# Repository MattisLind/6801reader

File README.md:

# 6801reader
This project aims at reading the ROM content out of a mask programmed MC6801 uP used in the Ericsson PC keyboard.

To help the MAME project to create a faithful emulation of the Ericsson PC I was asked to dump the ROM contents of a mask programmed 
6801 uProcessor which is the brain inside the keyboard. Compared to standard IBM PC the Ericsson PC make use of a completely different keyboard protocol
The protocol has standard serial communication rather than the clocked shiftregister approach in the IBM PC. In the receiving end on the mainboard there is a 8251 
serial communication IC. Dumping the keyboard and then emulating the MC6801 uProcessor inside MAME would then give a complete and faithful emulation of 
thenentire Ericsson PC.

## Dumping the 6801
Masked ROM can be a bit tricky to read out. On some uProcessor it isn't possible at all. On the 6801 there is a test mode 0 which 
makes the processor to behave a bit odd. It sets  the processor in non multiplexed mode which means that the 8 IO ports are the upper 8 bits of the address.
Then another IO port is the multiplexed Data and Adress bus for the lower 8 bits of the address. This is quite standard, but there
is another tweak that makes it possible to do the reading. In mode 0 it will also read the RESET vector from the external bus. It will disable reading
of the internal ROM for the two first cycles, thereby allowing external logic to map in external ROM for these two cycles and have the 
processor start the external program.

The external program can then be used to read all of the internal memory. Including the RESET vectors since after the two first access the internal address decoding goes back to
normal and the internal ROM RESET vectors can be read.

## Design

Adress decoding need special treatment during the first two cycles. This is achieved by a shiftregister that is shifting the RESET
signal when it transits from active to inactive. The three stage shiftregister is clocked by the negative edge of the E signal.
The result will be a delayed RESET signal. As long as the delayed RESET signal is low the deccoding will map addresses in the F800-FFFF range to
the external EPROM. After this period this decoding will be disabled and only accesses to F000-F7FF will be decoded as external.

The logic to handle the decoding and the shiftregister is implemented in a GAL16V8 PLD. The PLD also is used to debounce the RESET 
signal from the toggle switch.

## Firmware

The firmware used is a small debug monitor developed by Daniel Tufvesson [called MC3 monitor](http://www.waveguide.se/?article=mc3-monitor-13) which is modified 
to handle different memory locations for ROM and RAM. The 2.4576 MHz crystal result in a 4800 bps rate of the serial port.

The monitor can then be used to dump the ROM contents and transfer it to the host PC over the serial port.

The 2764 is a 8k EPROM with total address range 0000-1FFF.
This means that the 2k monitor code need to be in BOTH the 1000-17FF range and the 1800-1FFF range for the design to work. I.e. during the first two cycles it will access the 1800-1FFF range and after that the 1000-17FF range will be accessed. Actually repeating the monitor on all four 2k banks of the EPROM wouldn't harm at all. The PLD will select the proper range.

## Schemtic and layout.

A schematic has been created in KiCAD and a breadboard circuit. Possibly a layout is created as well.

## Mockup 

A mockup was created on a breadboard and a small problem was detected in the PLD. New PLD code fixed that problem. It was also detected that 68701 is sufficently different from the 6801 to not work with this circuit. The reason is that the 68701 has the interrupt vectors in a different place when running in mode 0. The 6803, which is the romless variant of the 6801, does work identical to the 6801. As it turns out it works perfectly with the circuit above. One interesting thing is that there actually are ROM content in the ROM which seems to be at least potentially correct. At least the RESET vector is in the correct spot! So it seems the 6803 is just 6801 chips which has been discarded due to bad firmware!? 

With the baudrate set to 4800 bps a 6803 or a 6801 processor gave us a ">" prompt in response to pressing the reset button. It was working! 

The resulting dump of the Ericsson keyboard 6801 firmware contained some interesting strings!

## PCB layout

A modified design and PCB layout were created with KiCad 9.0. The main change was to add a FT232 USB to serial IC. Additionally, A11 was reconnected to the EPROM, requiring the ROM to be put in all four banks as suggested above.

(modified design and layout by Tom Virostek (xuulan))

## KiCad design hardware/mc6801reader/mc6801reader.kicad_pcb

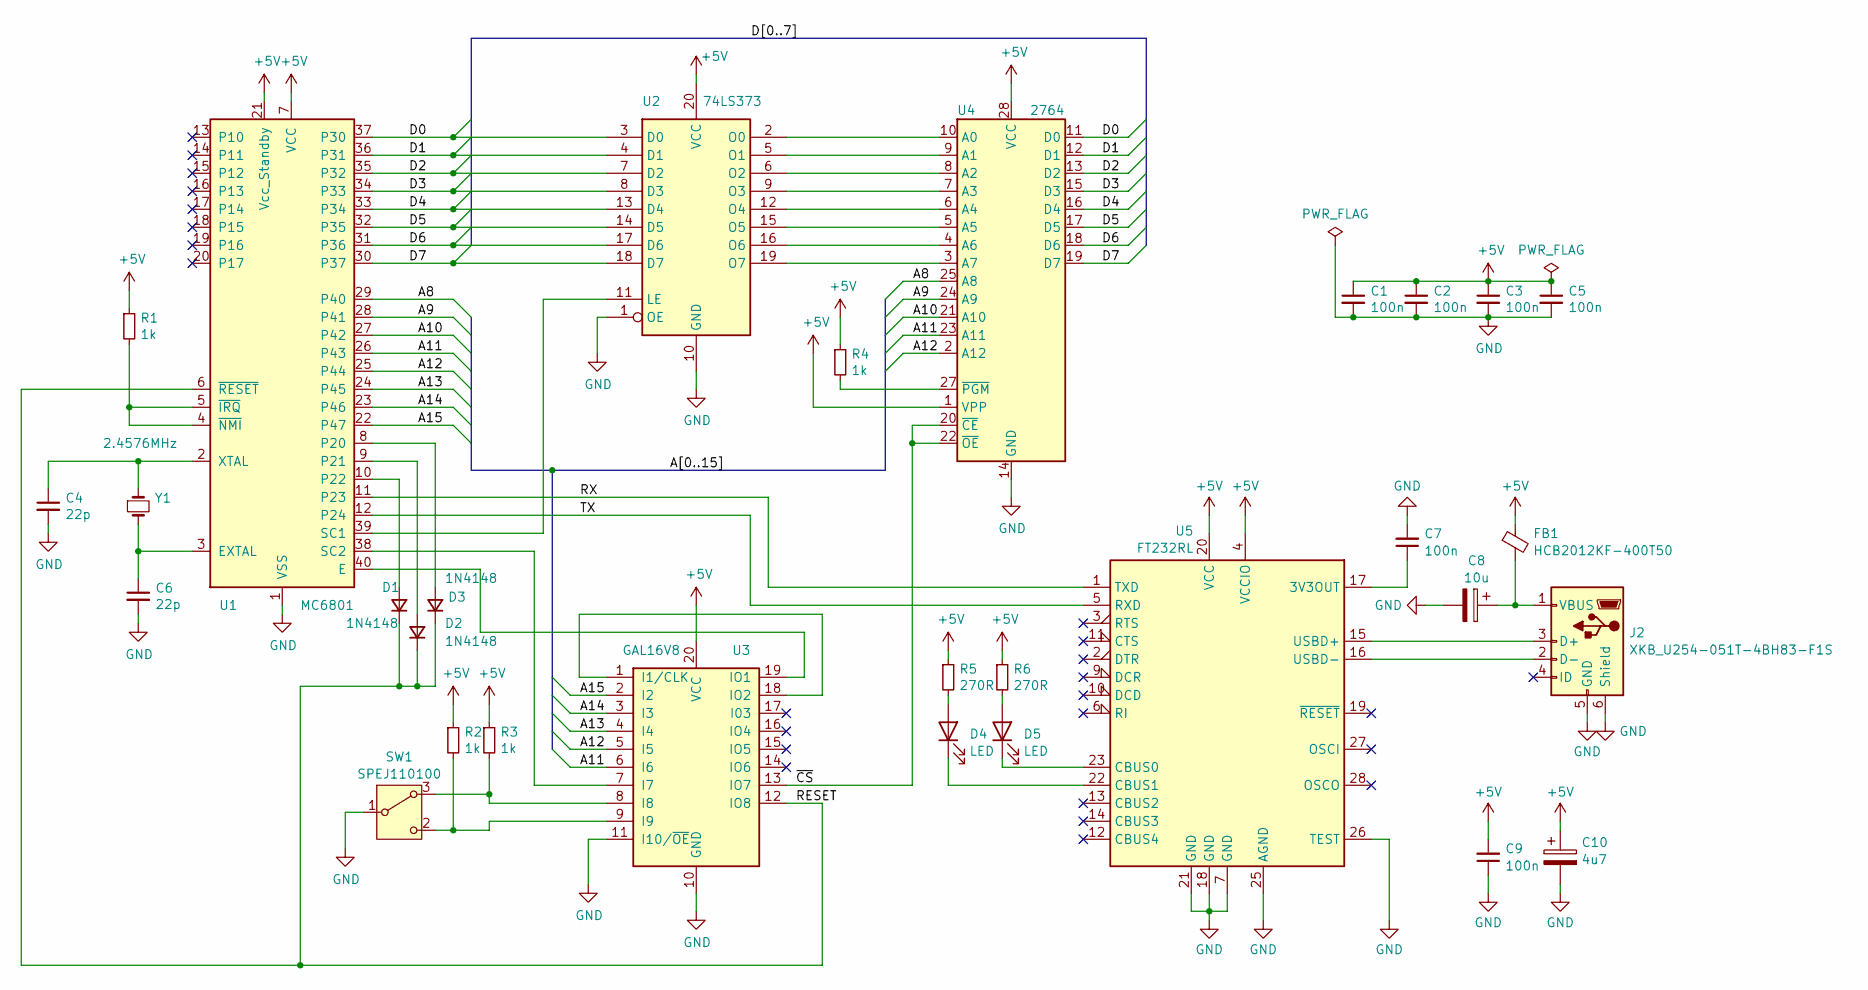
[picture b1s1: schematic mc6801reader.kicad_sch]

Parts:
C1, C2, C3, C5, C7, C9: 100n; C_0805_2012Metric
C4, C6: 22p; C_0805_2012Metric
C8: 10u; CP_EIA-3216-18_Kemet-A
C10: 4u7; CP_EIA-3216-18_Kemet-A
D1, D2, D3: 1N4148; D_SOD-323
D4, D5: LED; LED_0805_2012Metric
FB1: HCB2012KF-400T50; L_0805_2012Metric
J2: XKB_U254-051T-4BH83-F1S; USB_Micro-B_XKB_U254-051T-4BH83-F1S
R1, R2, R3, R4: 1k; R_0805_2012Metric
R5, R6: 270R; R_0805_2012Metric
SW1: SPEJ110100
U1: MC6801; DIP-40_W15.24mm
U2: 74LS373; SOIC-20W_7.5x12.8mm_P1.27mm
U3: GAL16V8; DIP-20_W7.62mm_Socket
U4: 2764; DIP-28_W15.24mm
U5: FT232RL; SSOP-28_5.3x10.2mm_P0.65mm
Y1: 2.4576MHz; Crystal_HC49-U_Vertical

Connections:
+5V: C1.1, C2.1, C3.1, C5.1, C9.2, C10.1, FB1.1, R1.1, R2.1, R3.1, R4.1, R5.1, R6.1, U1.7 (VCC), U1.21 (Vcc_Standby), U2.20 (VCC), U3.20 (VCC), U4.1 (VPP), U4.28 (VCC), U5.4 (VCCIO), U5.20 (VCC)
/A8: U1.29 (P40), U4.25 (A8)
/A9: U1.28 (P41), U4.24 (A9)
/A10: U1.27 (P42), U4.21 (A10)
/A11: U1.26 (P43), U3.6 (I6), U4.23 (A11)
/A12: U1.25 (P44), U3.5 (I5), U4.2 (A12)
/A13: U1.24 (P45), U3.4 (I4)
/A14: U1.23 (P46), U3.3 (I3)
/A15: U1.22 (P47), U3.2 (I2)
/D0: U1.37 (P30), U2.3 (D0), U4.11 (D0)
/D1: U1.36 (P31), U2.4 (D1), U4.12 (D1)
/D2: U1.35 (P32), U2.7 (D2), U4.13 (D2)
/D3: U1.34 (P33), U2.8 (D3), U4.15 (D3)
/D4: U1.33 (P34), U2.13 (D4), U4.16 (D4)
/D5: U1.32 (P35), U2.14 (D5), U4.17 (D5)
/D6: U1.31 (P36), U2.17 (D6), U4.18 (D6)
/D7: U1.30 (P37), U2.18 (D7), U4.19 (D7)
/RESET: D1.1 (K), D2.1 (K), D3.1 (K), U1.6 (~RESET), U3.12 (IO8)
/RX: U1.11 (P23), U5.1 (TXD)
/TX: U1.12 (P24), U5.5 (RXD)
/~CS: U3.13 (IO7), U4.20 (~CE), U4.22 (~OE)
GND: C1.2, C2.2, C3.2, C4.2, C5.2, C6.2, C7.2, C8.2, C9.1, C10.2, J2.5 (GND), J2.6 (Shield), SW1.1 (B), U1.1 (VSS), U2.1 (OE), U2.10 (GND), U3.10 (GND), U3.11 (I10/~OE), U4.14 (GND), U5.7 (GND), U5.18 (GND), U5.21 (GND), U5.25 (AGND), U5.26 (TEST)
unnamed: D1.2 (A), U1.10 (P22)
unnamed: D2.2 (A), U1.9 (P21)
unnamed: D3.2 (A), U1.8 (P20)
unnamed: D4.2 (A), R5.2
unnamed: D4.1 (K), U5.22 (CBUS1)
unnamed: D5.2 (A), R6.2
unnamed: D5.1 (K), U5.23 (CBUS0)
unnamed: J2.3 (D+), U5.15 (USBD+)
unnamed: J2.2 (D-), U5.16 (USBD-)
unnamed: C8.1, FB1.2, J2.1 (VBUS)
unnamed: R3.2, SW1.3 (A), U3.8 (I8)
unnamed: R2.2, SW1.2 (C), U3.9 (I9)
unnamed: U1.40 (E), U3.19 (IO1)
unnamed: C6.1, U1.3 (EXTAL), Y1.2
unnamed: U1.39 (SC1), U2.11 (LE)
unnamed: U1.38 (SC2), U3.7 (I7)
unnamed: C4.1, U1.2 (XTAL), Y1.1
unnamed: R1.2, U1.4 (~NMI), U1.5 (~IRQ)
unnamed: U2.2 (O0), U4.10 (A0)
unnamed: U2.5 (O1), U4.9 (A1)
unnamed: U2.6 (O2), U4.8 (A2)
unnamed: U2.9 (O3), U4.7 (A3)
unnamed: U2.12 (O4), U4.6 (A4)
unnamed: U2.15 (O5), U4.5 (A5)
unnamed: U2.16 (O6), U4.4 (A6)
unnamed: U2.19 (O7), U4.3 (A7)
unnamed: U3.1 (I1/CLK), U3.18 (IO2)
unnamed: R4.2, U4.27 (~PGM)
unnamed: C7.1, U5.17 (3V3OUT)

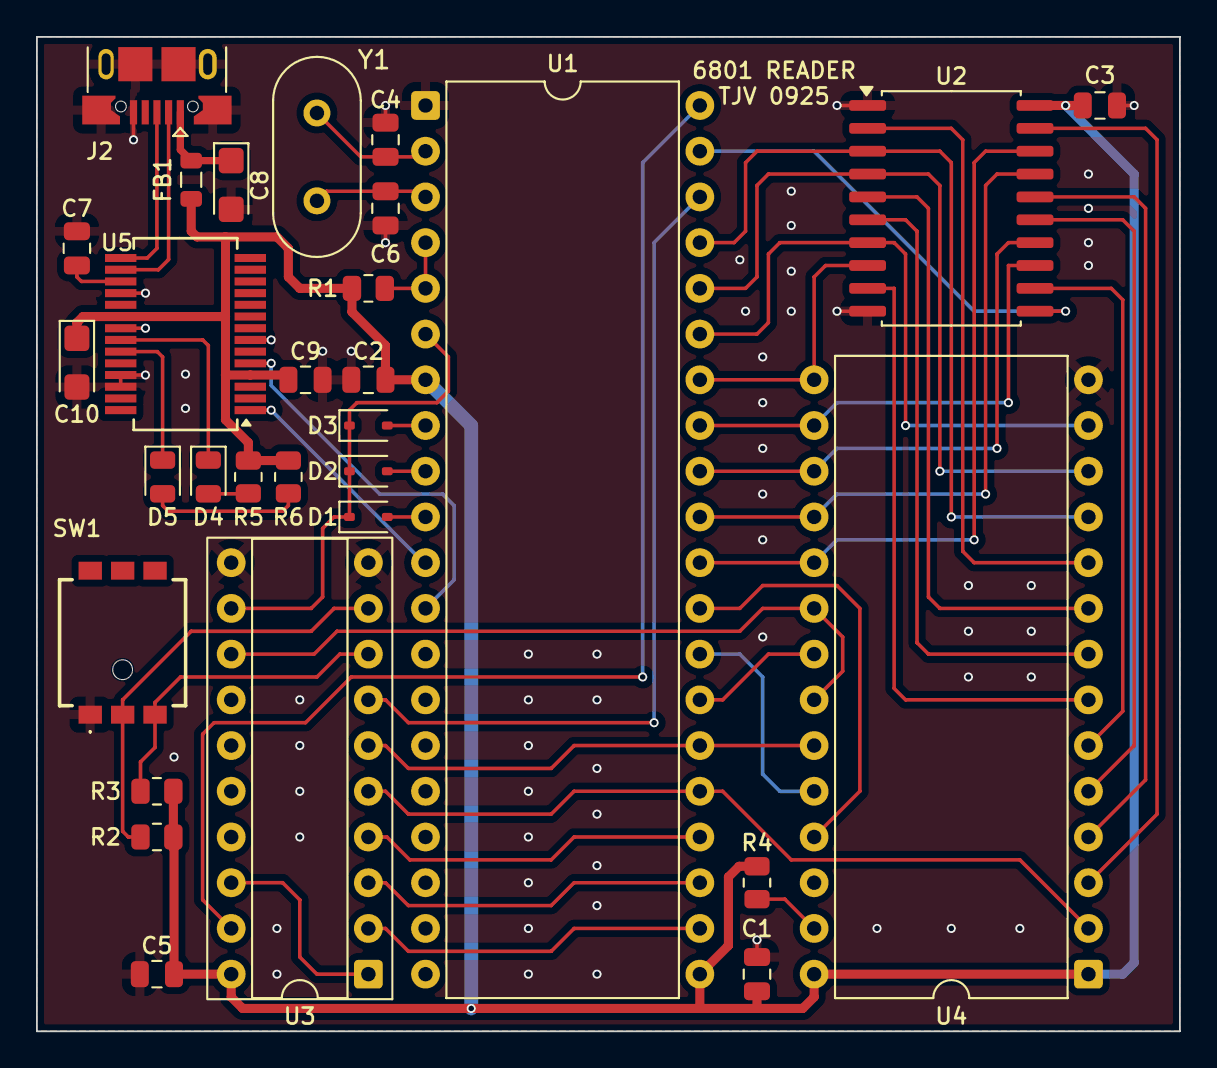
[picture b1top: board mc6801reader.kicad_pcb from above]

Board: 2 copper layers, 63.5 x 55.2 mm, 30 parts (0 on the bottom side), 51 nets.

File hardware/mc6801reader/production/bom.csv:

Designator,Footprint,Quantity,Value,LCSC Part #
"C1, C2, C3, C5, C7, C9",0805,6,100n,
C10,CP_EIA-3216-18_Kemet-A,1,4u7,
"C4, C6",0805,2,22p,
C8,CP_EIA-3216-18_Kemet-A,1,10u,
"D1, D2, D3",D_SOD-323,3,1N4148,
"D4, D5",0805,2,LED,
FB1,0805,1,HCB2012KF-400T50,
J2,USB_Micro-B_XKB_U254-051T-4BH83-F1S,1,XKB_U254-051T-4BH83-F1S,
"R1, R2, R3, R4",0805,4,1k,
"R5, R6",0805,2,270R,
SW1,SPEJ110100,1,SPEJ110100,
U1,DIP-40_W15.24mm,1,MC6801,
U2,SOIC-20W_7.5x12.8mm_P1.27mm,1,74LS373,
U3,DIP-20_W7.62mm_Socket,1,GAL16V8,
U4,DIP-28_W15.24mm,1,2764,
U5,SSOP-28_5.3x10.2mm_P0.65mm,1,FT232RL,
Y1,Crystal_HC49-U_Vertical,1,2.4576MHz,

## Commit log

2019-08-29 Create README.md
    First draft of README file
2019-08-29 Update README.md
    Added more on RESET signal.
2019-08-29 Added picture of keyboard
2019-08-29 First draft of design of hardware
2019-08-29 Added PLD files
2019-08-29 Added pdf file for the schematic.
2019-08-29 Added schematic
2019-08-29 Now the right schematic instead.
2019-08-30 initial commit of 68xx cross assembler suite
2019-08-30 initial commit of modified mc3 sources and readme.txt file
2019-09-07 Fix E as part of CS and inverting E clock
2019-09-07 Updated schematic to reflect changes in PLD code
2019-09-07 Updated readme with new schematic, added pictures.
2019-09-07 Fixed some texts.
2019-09-07 Fixed some readme textx.
2019-09-08 Revert "initial commit of modified mc3 sources and readme.txt file"
    This reverts commit 6e638a57c6289ee04c5ef6d2a7f7fe1bfef9992b.
2019-09-08 mc3: original version 1.4.1
2019-09-08 reissued commit of mc3 sources to get diff from original to ease updates of mc3 later
2019-09-11 A11 is grounded
2019-09-11 Added jpg
2019-09-13 Updated pdf and jpg file again
2019-09-13 Updated readme with new jpg
2022-08-21 Added info on monitor location
    The monitor need to be repeated twice in the EPROM.
2025-12-29 Modify design and create PCB layout.
2026-02-10 Fix schematic image link in README
    Updated schematic image link in README.
